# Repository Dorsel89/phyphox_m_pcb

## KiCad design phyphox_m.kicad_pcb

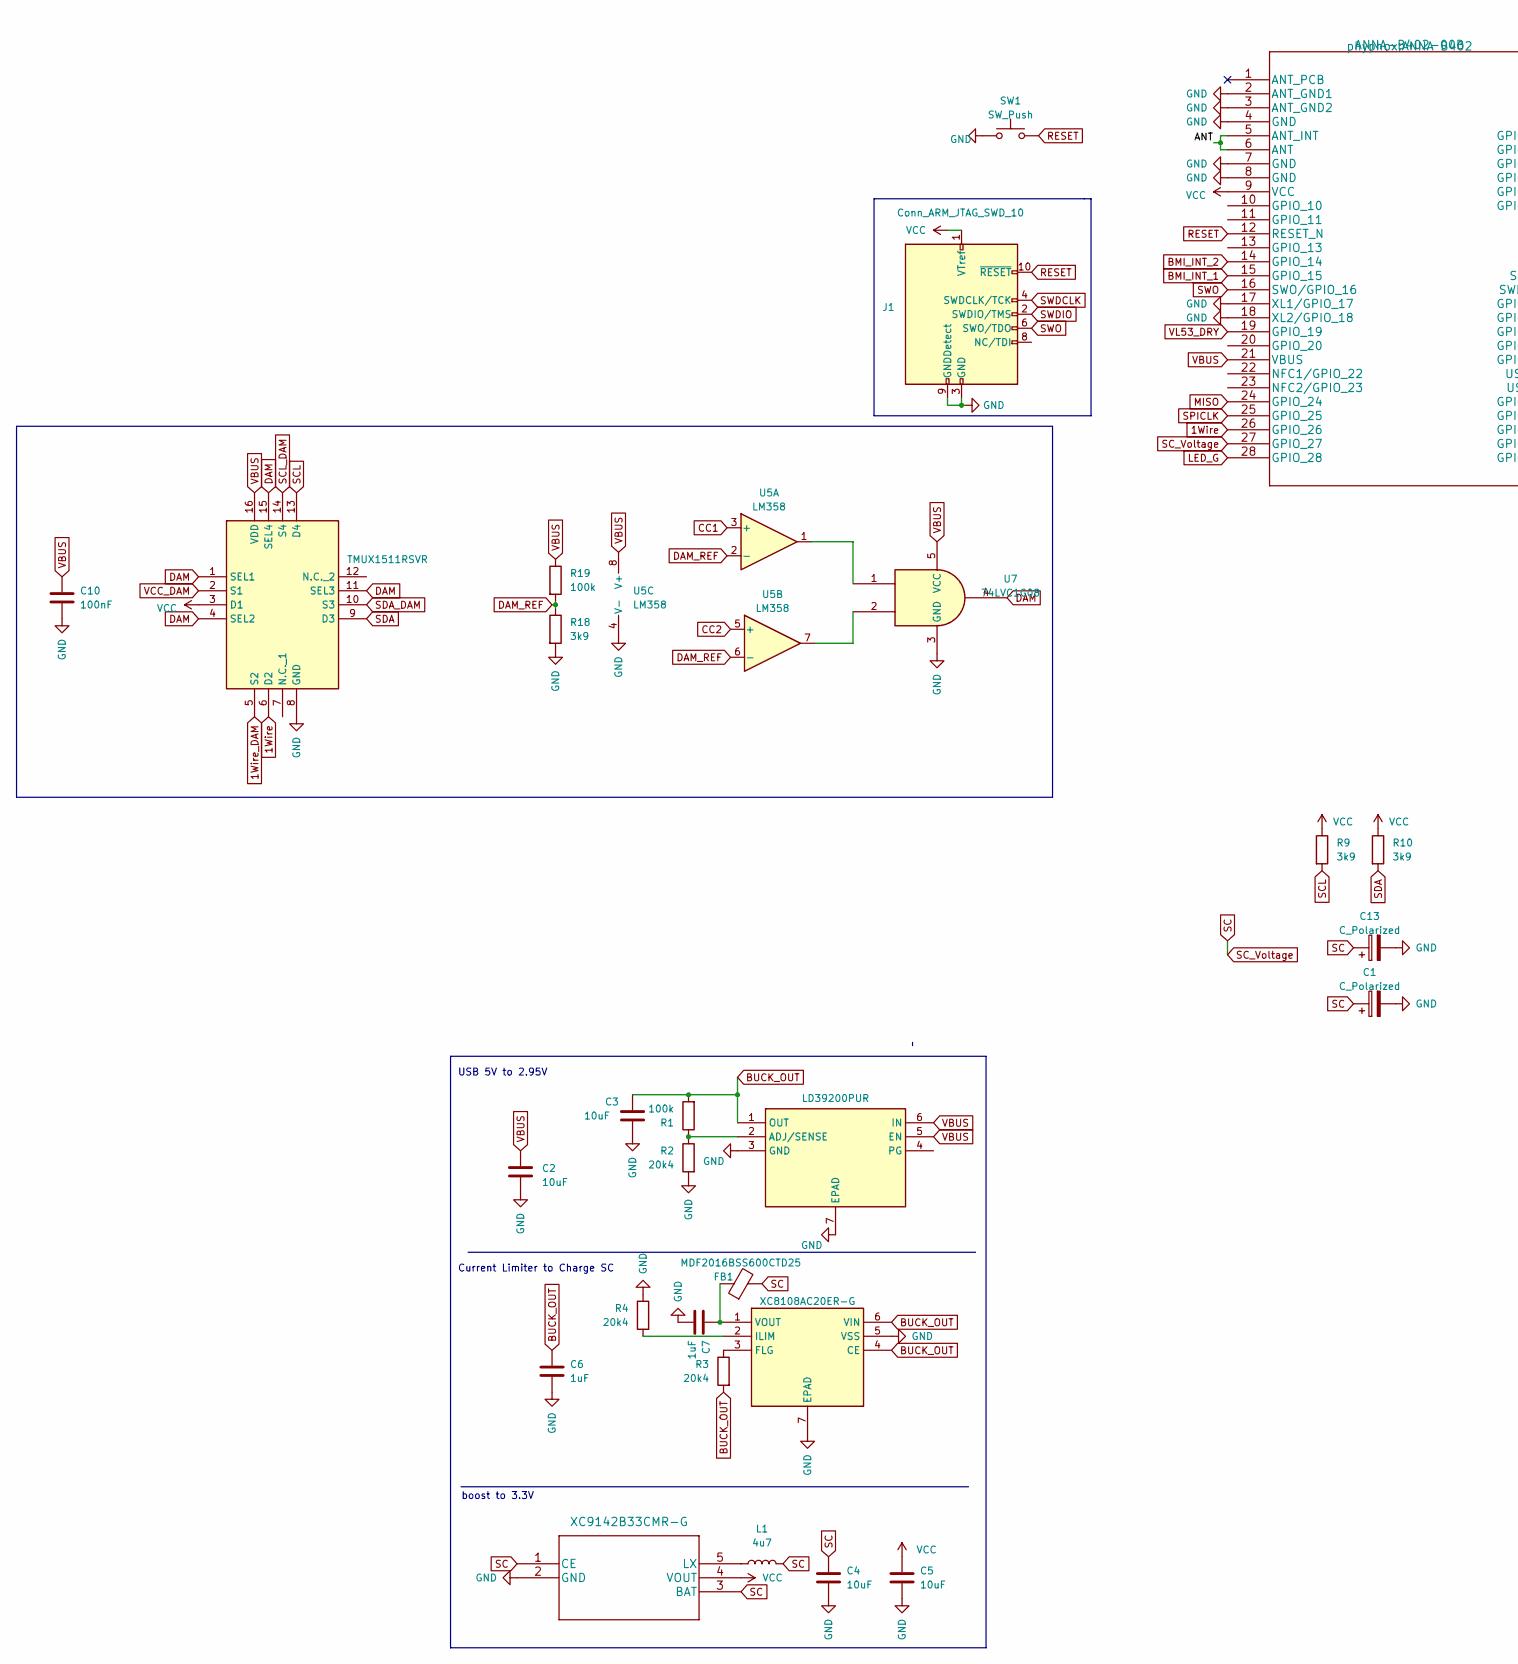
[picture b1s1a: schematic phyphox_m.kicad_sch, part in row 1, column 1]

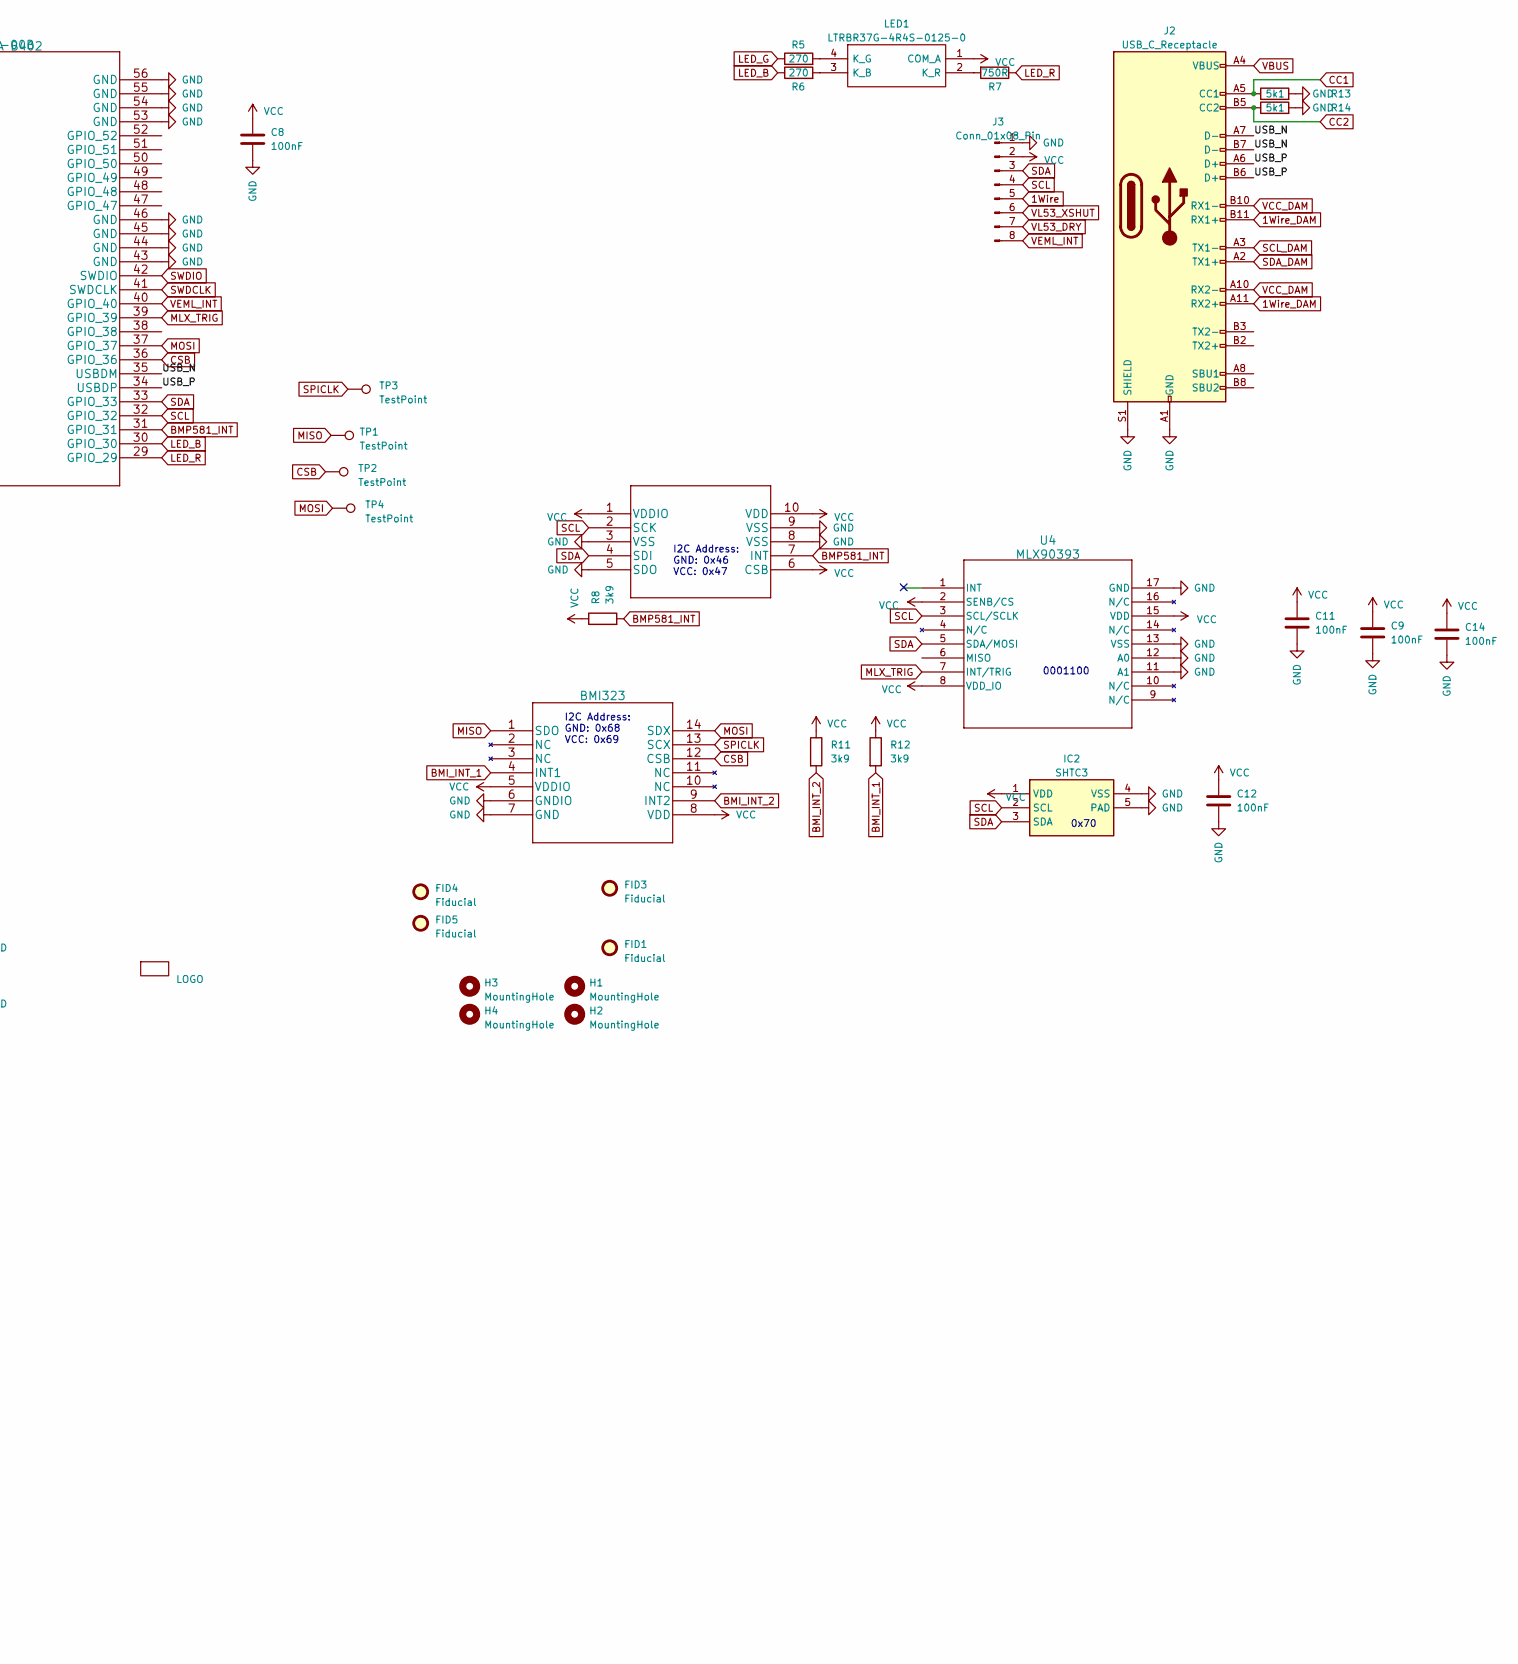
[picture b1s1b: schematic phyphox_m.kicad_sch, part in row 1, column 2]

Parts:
C1, C13: C_Polarized; SuperCap_DSF106Q3R0C
C2, C3, C4, C5: 10uF; C_0805_2012Metric
C6, C7: 1uF; C_0603_1608Metric
C8, C9, C10, C11, C12, C14: 100nF; C_0603_1608Metric
FB1: MDF2016BSS600CTD25; L_0805_2012Metric
FID1, FID3, FID4, FID5: Fiducial; Fiducial_0.5mm_Mask1mm
H1, H2, H3, H4: MountingHole; Keystone_8734
IC2: SHTC3; Mouser Part Number 403-SHTC3
IC3: LD39200PUR; SON95P300X300X100-7N-D; Mouser Part Number 511-LD39200PUR
IC6: TMUX1511RSVR; QFN40P180X260X55-16N; Mouser Part Number 595-TMUX1511RSVR
J1: Conn_ARM_JTAG_SWD_10; Tag-Connect_TC2050-IDC-NL_2x05_P1.27mm_Vertical
J2: USB_C_Receptacle; USB_C_Receptacle_Molex_105450-0101
J3: Conn_01x08_Pin; PinSocket_1x08_P1.00mm_Vertical_SMD_Pin1Left
L1: 4u7; IND_LQH5BPN4R7NT0L
LED1: LTRBR37G-4R4S-0125-0; LTRBR37G4R4S01250; Mouser Part Number 720-LTRBR37GA6714
R1, R19: 100k; R_0603_1608Metric
R2, R3, R4: 20k4; R_0603_1608Metric
R5, R6: 270; R_0603_1608Metric
R7: 750R; R_0603_1608Metric
R8, R9, R10, R11, R12, R18: 3k9; R_0603_1608Metric
R13, R14: 5k1; R_0603_1608Metric
S1: XC8108AC20ER-G; SON50P200X180X60-7N; Mouser Part Number 865-XC8108AC20ER-G
SW1: SW_Push; EVQP7J01P
TP1, TP2, TP3, TP4: TestPoint; TestPoint_Pad_D1.0mm
U1: ANNA-B402-00B; ANNA B402
U2: BMI323
U3: BMP581
U4: MLX90393
U5: LM358; SOT-23-8
U6: XC9142B33CMR-G
U7: 74LVC1G08; SOT-353_SC-70-5
Z1: LOGO; logo_6x6mm

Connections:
1Wire: IC6.6 (D2), J3.5, U1.26 (GPIO_26)
1Wire_DAM: IC6.5 (S2), J2.A11 (RX2+), J2.B11 (RX1+)
/ANT: U1.5 (ANT_INT), U1.6 (ANT)
/USB_N: J2.A7 (D-), J2.B7 (D-), U1.35 (USBDM)
/USB_P: J2.A6 (D+), J2.B6 (D+), U1.34 (USBDP)
BMI_INT_1: R12.2, U1.15 (GPIO_15), U2.4 (INT1)
BMI_INT_2: R11.2, U1.14 (GPIO_14), U2.9 (INT2)
BMP581_INT: R8.2, U1.31 (GPIO_31), U3.7 (INT)
BUCK_OUT: C3.2, C6.1, IC3.1 (OUT), R1.2, R3.2, S1.4 (CE), S1.6 (VIN)
CC1: J2.A5 (CC1), R13.1, U5.3 (+)
CC2: J2.B5 (CC2), R14.1, U5.5 (+)
CSB: TP2.1, U1.36 (GPIO_36), U2.12 (CSB)
DAM: IC6.1 (SEL1), IC6.4 (SEL2), IC6.11 (SEL3), IC6.15 (SEL4), U7.4
DAM_REF: R18.1, R19.2, U5.2 (-), U5.6 (-)
GND: C1.2, C2.2, C3.1, C4.2, C5.2, C6.2, C7.2, C8.2, C9.2, C10.2, C11.2, C12.2, C13.2, C14.2, IC2.4 (VSS), IC2.5 (PAD), IC3.3 (GND), IC3.7 (EPAD), IC6.8 (GND), J1.3 (GND), J1.5 (GND), J1.9 (GNDDetect), J2.A1 (GND), J2.A12 (GND), J2.B1 (GND), J2.B12 (GND), J2.S1 (SHIELD), J3.1, R2.2, R4.1, R13.2, R14.2, R18.2, S1.5 (VSS), S1.7 (EPAD), SW1.1, U1.2 (ANT_GND1), U1.3 (ANT_GND2), U1.4 (GND), U1.7 (GND), U1.8 (GND), U1.17 (XL1/GPIO_17), U1.18 (XL2/GPIO_18), U1.43 (GND), U1.44 (GND), U1.45 (GND), U1.46 (GND), U1.53 (GND), U1.54 (GND), U1.55 (GND), U1.56 (GND), U2.6 (GNDIO), U2.7 (GND), U3.3 (VSS), U3.5 (SDO), U3.8 (VSS), U3.9 (VSS), U4.11 (A1), U4.12 (A0), U4.13 (VSS), U4.17 (GND), U5.4 (V-), U6.2 (GND), U7.3 (GND)
LED_B: R6.1, U1.30 (GPIO_30)
LED_G: R5.1, U1.28 (GPIO_28)
LED_R: R7.1, U1.29 (GPIO_29)
MISO: TP1.1, U1.24 (GPIO_24), U2.1 (SDO)
MLX_TRIG: U1.39 (GPIO_39), U4.7 (INT/TRIG)
MOSI: TP4.1, U1.37 (GPIO_37), U2.14 (SDX)
unnamed: IC3.2 (ADJ/SENSE), R1.1, R2.1
unnamed: LED1.3 (K_B), R6.2
unnamed: LED1.4 (K_G), R5.2
unnamed: LED1.2 (K_R), R7.2
unnamed: R3.1, S1.3 (FLG)
unnamed: R4.2, S1.2 (ILIM)
unnamed: C7.1, FB1.1, S1.1 (VOUT)
unnamed: U5.1, U7.1
unnamed: U5.7, U7.2
unnamed: L1.1, U6.5 (LX)
RESET: J1.10 (~RESET), SW1.2, U1.12 (RESET_N)
SC: C1.1, C4.1, C13.1, FB1.2, L1.2, U1.27 (GPIO_27), U6.1 (CE), U6.3 (BAT)
SCL: IC2.2 (SCL), IC6.13 (D4), J3.4, R9.2, U1.32 (GPIO_32), U3.2 (SCK), U4.3 (SCL/SCLK)
SCL_DAM: IC6.14 (S4), J2.A3 (TX1-)
SDA: IC2.3 (SDA), IC6.9 (D3), J3.3, R10.2, U1.33 (GPIO_33), U3.4 (SDI), U4.5 (SDA/MOSI)
SDA_DAM: IC6.10 (S3), J2.A2 (TX1+)
SPICLK: TP3.1, U1.25 (GPIO_25), U2.13 (SCX)
SWDCLK: J1.4 (SWDCLK/TCK), U1.41 (SWDCLK)
SWDIO: J1.2 (SWDIO/TMS), U1.42 (SWDIO)
SWO: J1.6 (SWO/TDO), U1.16 (SWO/GPIO_16)
VBUS: C2.1, C10.1, IC3.5 (EN), IC3.6 (IN), IC6.16 (VDD), J2.A4 (VBUS), J2.A9 (VBUS), J2.B4 (VBUS), J2.B9 (VBUS), R19.1, U1.21 (VBUS), U5.8 (V+), U7.5 (VCC)
VCC: C5.1, C8.1, C9.1, C11.1, C12.1, C14.1, IC2.1 (VDD), IC6.3 (D1), J1.1 (VTref), J3.2, LED1.1 (COM_A), R8.1, R9.1, R10.1, R11.1, R12.1, U1.9 (VCC), U2.5 (VDDIO), U2.8 (VDD), U3.1 (VDDIO), U3.6 (CSB), U3.10 (VDD), U4.2 (SENB/CS), U4.8 (VDD_IO), U4.15 (VDD), U6.4 (VOUT)
VCC_DAM: IC6.2 (S1), J2.A10 (RX2-), J2.B10 (RX1-)
VEML_INT: J3.8, U1.40 (GPIO_40)
VL53_DRY: J3.7, U1.19 (GPIO_19)
VL53_XSHUT: J3.6

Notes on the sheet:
0x70
I2C Address: GND: 0x68 VCC: 0x69
Current Limiter to Charge SC
0001100
boost to 3.3V
I2C Address: GND: 0x46 VCC: 0x47
USB 5V to 2.95V

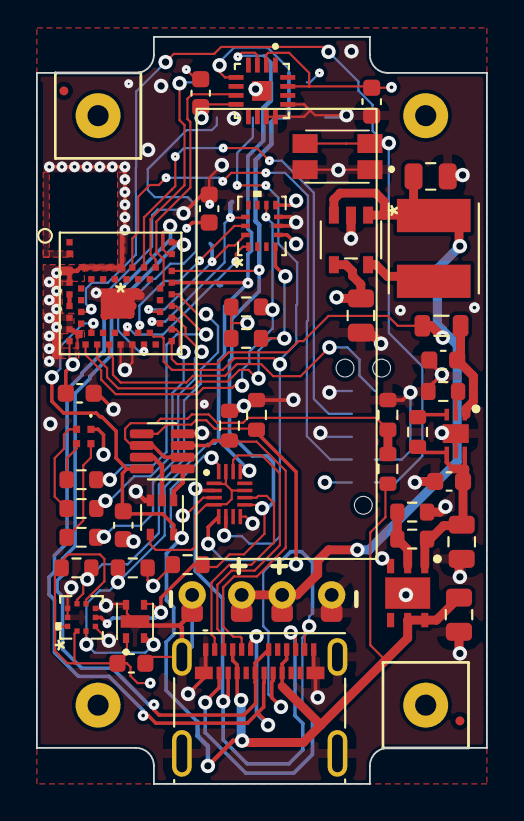
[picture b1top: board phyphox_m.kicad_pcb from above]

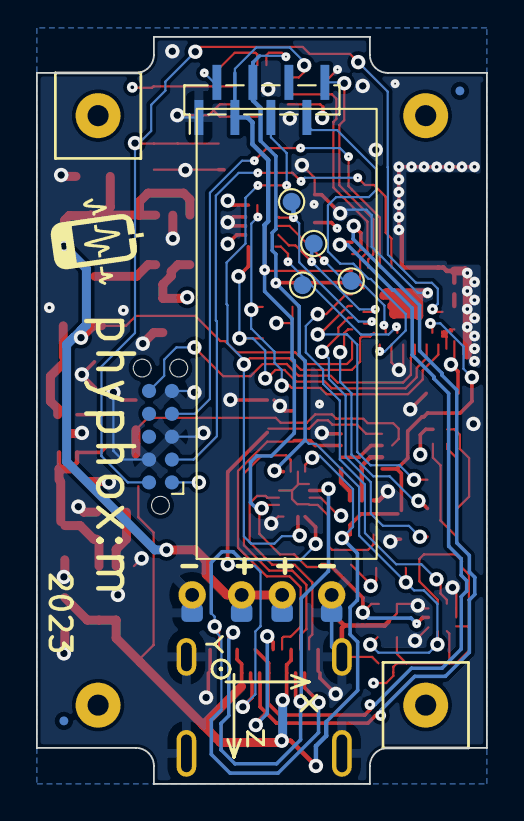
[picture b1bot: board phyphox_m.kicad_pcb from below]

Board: 4 copper layers, 25.0 x 41.5 mm, 61 parts (12 on the bottom side), 46 nets.

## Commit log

2023-10-13 init

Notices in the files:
parts and their libraries:
Copyright 2021 Accelerated Designs. All rights reserved.
